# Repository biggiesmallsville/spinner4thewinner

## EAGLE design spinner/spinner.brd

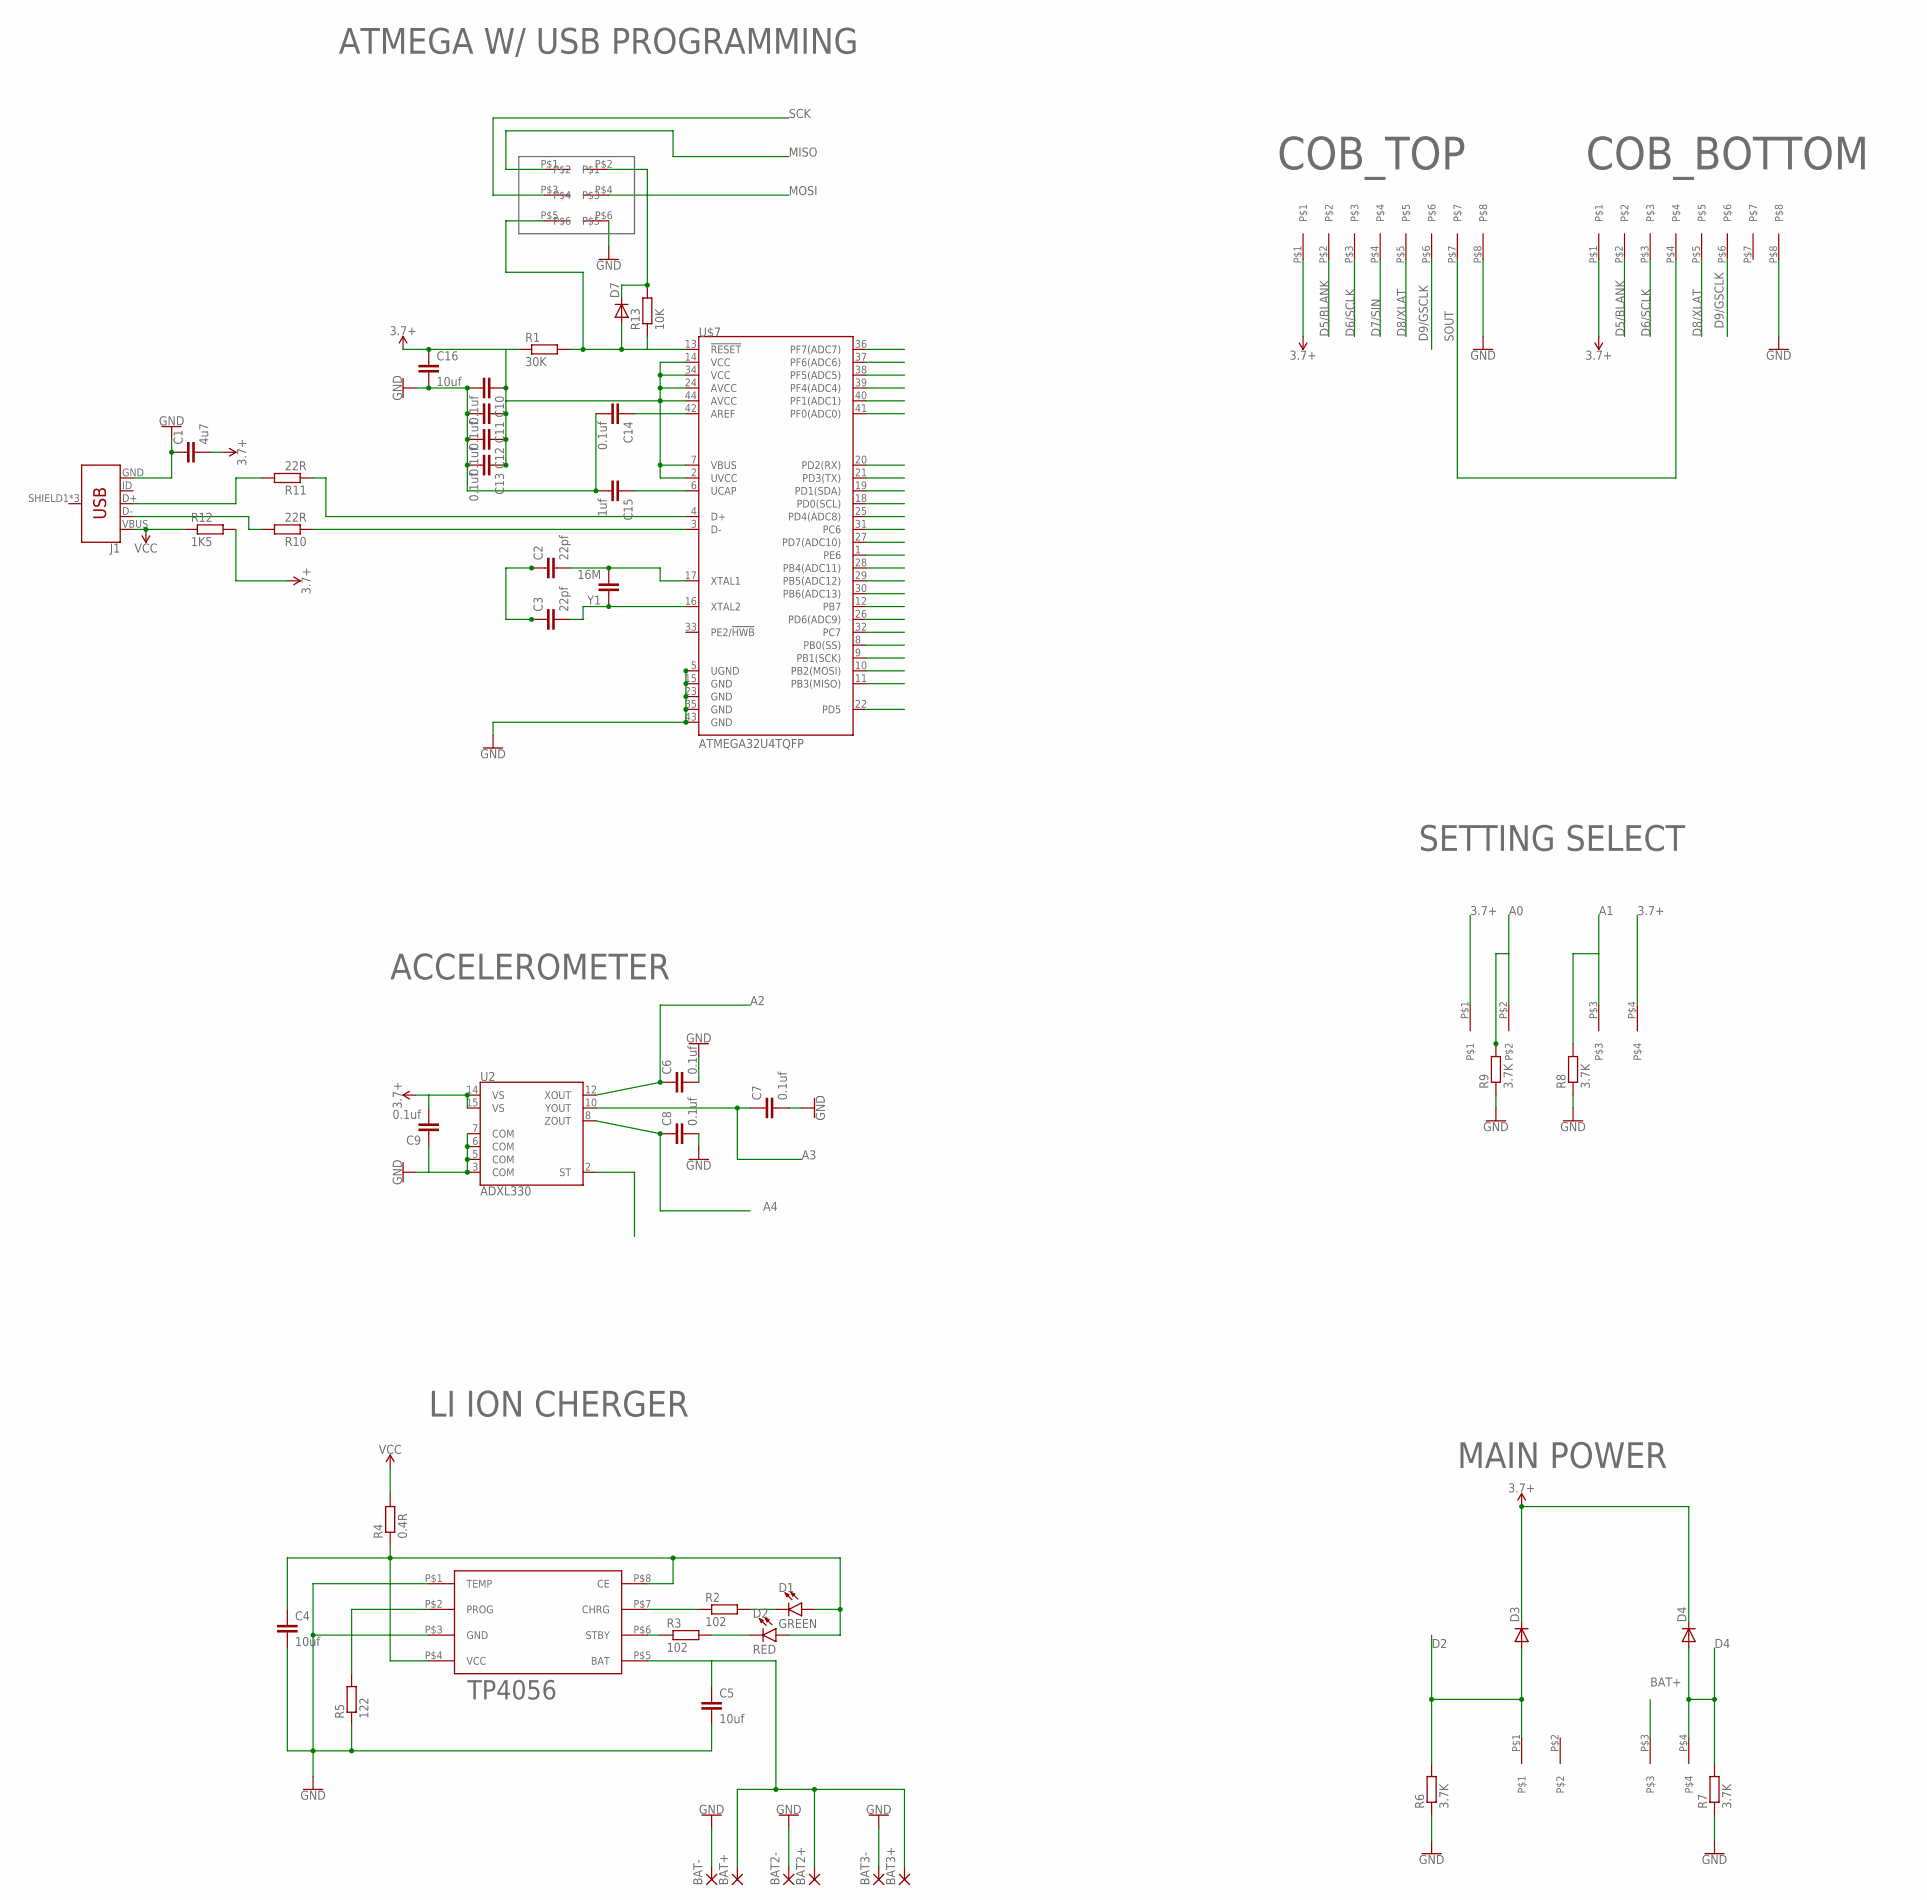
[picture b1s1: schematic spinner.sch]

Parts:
BAT2+, BAT2-, BAT3+, BAT3-: SMD2; SMD1,27-2,54
BAT+: SMD2; SMD1,27-2,54
BAT-: SMD2; SMD1,27-2,54
C1: 4u7; C0603
C2, C3: 22pf; C0603
C4, C5, C16: 10uf; C0603
C6, C7, C8, C9, C10, C11, C12, C13, C14: 0.1uf; C0603
C15: 1uf; C0603
D1: GREEN; LED-0603
D2: RED; LED-0603
D3, D4, D7: DIODE-SOD123; SOD123
J1: USB_MICRO-BREDUCED_PASTE; USB-B-MICRO-SMD_RED_PASTE
R1: 30K; R0603
R2, R3: 102; R0603
R4: 0.4R; R0603
R5: 122; R0603
R6, R7, R8, R9: 3.7K; R0603
R10, R11: 22R; R0603
R12: 1K5; R0603
R13: 10K; R0603
U2: ADXL330; LFCSP-16-4X4
U$1, U$2: SLIDE_SWITCH
U$3: TP4056
U$6: ICSP
U$7: ATMEGA32U4TQFP; SPARKFUN-DIGITALIC_TQFP44
U$8, U$9: 8PIN
Y1: 16M; C0603

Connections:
3.7+: C1.2, C9.2, C10.1, C11.1, C12.1, C13.1, C16.1, D3.C, D4.C, R1.1, R12.2, U2.14 (VS), U2.15 (VS), U$1.P$1, U$1.P$4, U$7.2 (UVCC), U$7.7 (VBUS), U$7.14 (VCC), U$7.24 (AVCC), U$7.34 (VCC), U$7.44 (AVCC), U$8.P$1, U$9.P$1
A0: R9.2, U$1.P$2, U$7.36 (PF7(ADC7))
A1: R8.2, U$1.P$3, U$7.37 (PF6(ADC6))
A2: C6.1, U2.12 (XOUT), U$7.38 (PF5(ADC5))
A3: C7.1, U2.10 (YOUT), U$7.39 (PF4(ADC4))
A4: C8.1, U2.8 (ZOUT), U$7.40 (PF1(ADC1))
A5: U$7.41 (PF0(ADC0))
BAT+: BAT2+.1, BAT3+.1, BAT+.1, C5.1, U$2.P$3, U$3.P$5 (BAT)
D0: U$7.20 (PD2(RX))
D1: U$7.21 (PD3(TX))
D2: D3.A, R6.2, U$2.P$1, U$7.19 (PD1(SDA))
D3: U$7.18 (PD0(SCL))
D4: D4.A, R7.2, U$2.P$4, U$7.25 (PD4(ADC8))
D5/BLANK: U$7.31 (PC6), U$8.P$2, U$9.P$2
D6/SCLK: U$7.27 (PD7(ADC10)), U$8.P$3, U$9.P$3
D7/SIN: U$7.1 (PE6), U$8.P$4
D8/XLAT: U$7.28 (PB4(ADC11)), U$8.P$5, U$9.P$5
D9/GSCLK: R11.1, U$7.4 (D+), U$7.29 (PB5(ADC12)), U$8.P$6, U$9.P$6
D10: U$7.30 (PB6(ADC13))
D11: U$7.12 (PB7)
D12: U$7.26 (PD6(ADC9))
D13: U$7.32 (PC7)
D17: U$7.8 (PB0(SS))
GND: BAT2-.1, BAT3-.1, BAT-.1, C1.1, C2.1, C3.1, C4.2, C5.2, C6.2, C7.2, C8.2, C9.1, C10.2, C11.2, C12.2, C13.2, C14.2, C15.2, C16.2, J1.GND, R5.1, R6.1, R7.1, R8.1, R9.1, U2.3 (COM), U2.5 (COM), U2.6 (COM), U2.7 (COM), U$3.P$1 (TEMP), U$3.P$3 (GND), U$6.P$6, U$7.5 (UGND), U$7.15 (GND), U$7.23 (GND), U$7.35 (GND), U$7.43 (GND), U$8.P$8, U$9.P$8
MISO: U$6.P$1, U$7.11 (PB3(MISO))
MOSI: U$6.P$4, U$7.10 (PB2(MOSI))
unnamed: C2.2, U$7.17 (XTAL1), Y1.2
unnamed: C3.2, U$7.16 (XTAL2), Y1.1
unnamed: D7.C, R13.2, U$6.P$2
unnamed: R5.2, U$3.P$2 (PROG)
unnamed: C4.1, D1.A, D2.A, R4.1, U$3.P$4 (VCC), U$3.P$8 (CE)
unnamed: J1.D-, R10.2
unnamed: R2.1, U$3.P$7 (CHRG)
unnamed: R3.1, U$3.P$6 (STBY)
unnamed: D2.C, R3.2
unnamed: D1.C, R2.2
unnamed: J1.D+, R11.2
unnamed: R10.1, U$7.3 (D-)
unnamed: C14.1, U$7.42 (AREF)
unnamed: C15.1, U$7.6 (UCAP)
RESET: D7.A, R1.2, R13.1, U$6.P$5, U$7.13 (!RESET)
SCK: U$6.P$3, U$7.9 (PB1(SCK))
SOUT: U$8.P$7, U$9.P$4
VCC: J1.VBUS, R4.2, R12.1

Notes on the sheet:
COB_TOP
COB_BOTTOM
SETTING SELECT
MAIN POWER
ACCELEROMETER
LI ION CHERGER
ATMEGA W/ USB PROGRAMMING

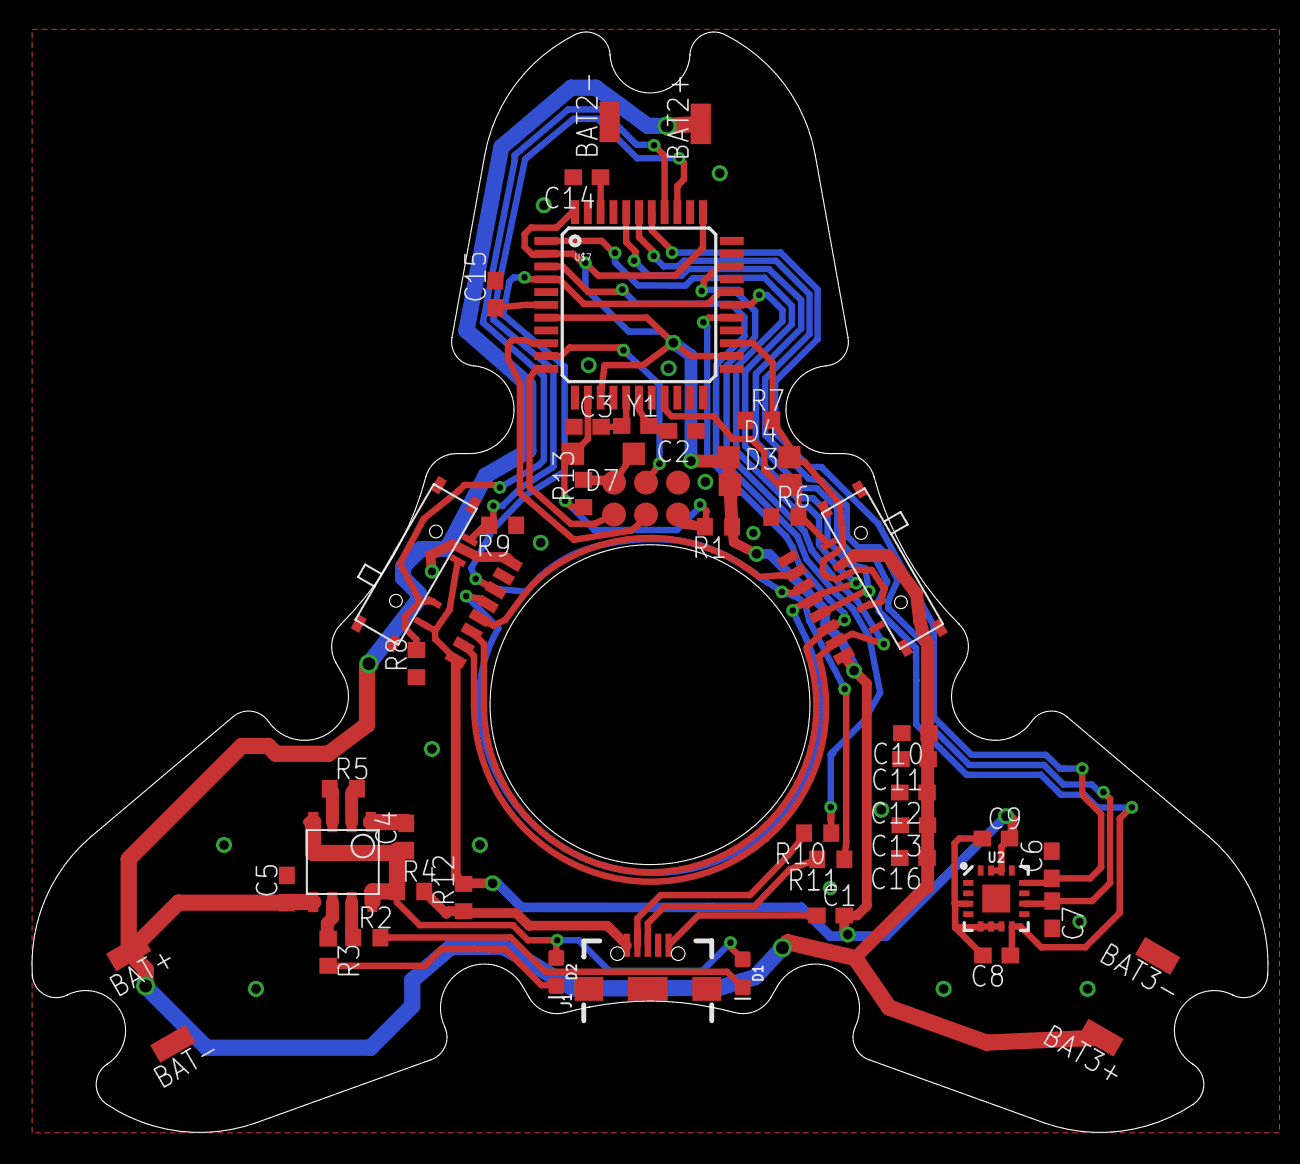
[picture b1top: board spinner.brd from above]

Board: 2 copper layers, 77.3 x 68.8 mm, 50 parts (0 on the bottom side), 35 nets.

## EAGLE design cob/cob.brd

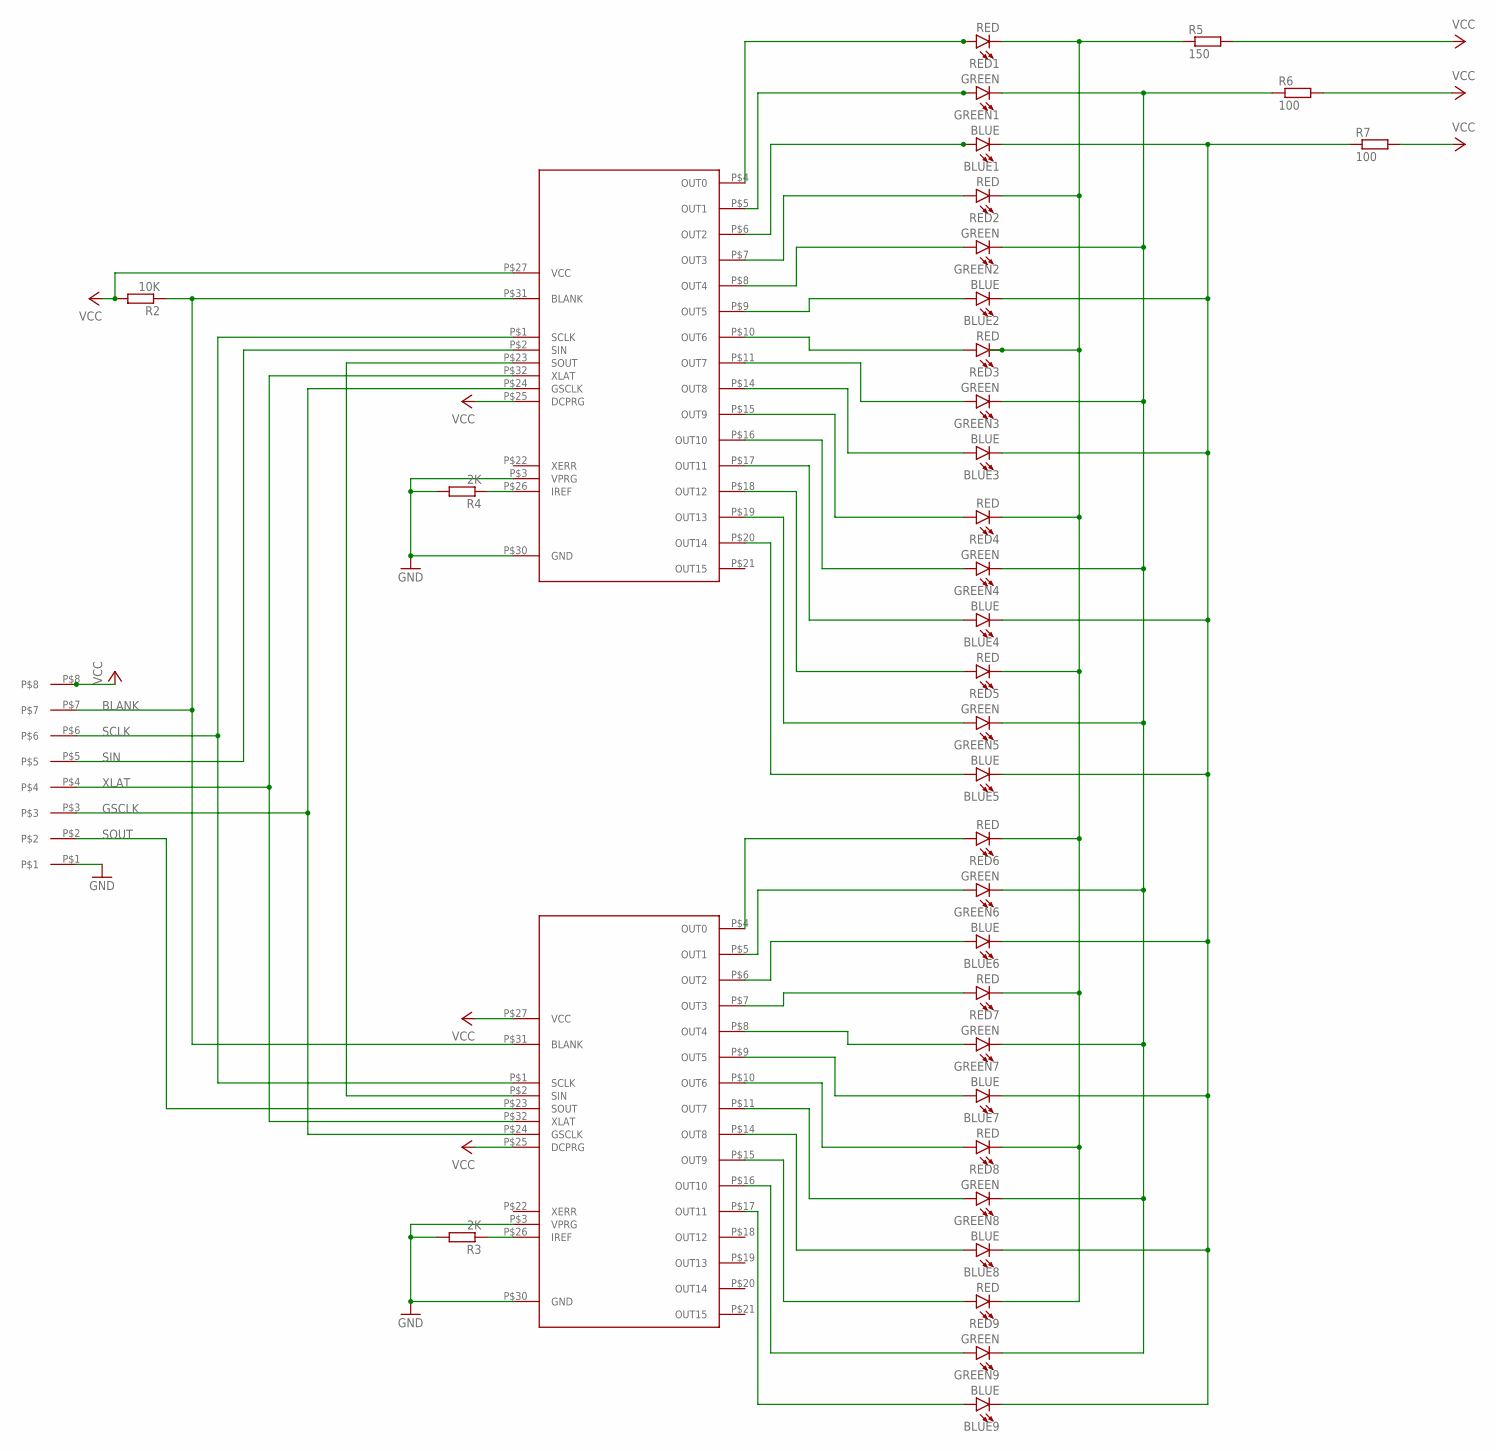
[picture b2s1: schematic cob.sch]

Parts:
BLUE1, BLUE2, BLUE3, BLUE4, BLUE5, BLUE6, BLUE7, BLUE8, BLUE9: BLUE; LED-0603
GREEN1, GREEN2, GREEN3, GREEN4, GREEN5, GREEN6, GREEN7, GREEN8, GREEN9: GREEN; LED-0603
R2: 10K; R0402
R3, R4: 2K; R0402
R5: 150; R1206
R6, R7: 100; R1206
RED1, RED2, RED3, RED4, RED5, RED6, RED7, RED8, RED9: RED; LED-0603
U$1, U$2: TLC5940; RHB
U$3: 8PIN

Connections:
BLANK: R2.1, U$1.P$31 (BLANK), U$2.P$31 (BLANK), U$3.P$7
GND: R3.2, R4.2, U$1.P$3 (VPRG), U$1.P$30 (GND), U$2.P$3 (VPRG), U$2.P$30 (GND), U$3.P$1
GSCLK: U$1.P$24 (GSCLK), U$2.P$24 (GSCLK), U$3.P$3
unnamed: RED1.A, U$1.P$4 (OUT0)
unnamed: GREEN1.A, U$1.P$5 (OUT1)
unnamed: RED2.A, U$1.P$7 (OUT3)
unnamed: R4.1, U$1.P$26 (IREF)
unnamed: R3.1, U$2.P$26 (IREF)
unnamed: BLUE3.A, U$1.P$14 (OUT8)
unnamed: BLUE2.A, U$1.P$9 (OUT5)
unnamed: U$1.P$23 (SOUT), U$2.P$2 (SIN)
unnamed: BLUE1.A, U$1.P$6 (OUT2)
unnamed: GREEN2.A, U$1.P$8 (OUT4)
unnamed: RED3.A, U$1.P$10 (OUT6)
unnamed: GREEN3.A, U$1.P$11 (OUT7)
unnamed: RED4.A, U$1.P$15 (OUT9)
unnamed: GREEN4.A, U$1.P$16 (OUT10)
unnamed: BLUE4.A, U$1.P$17 (OUT11)
unnamed: RED5.A, U$1.P$18 (OUT12)
unnamed: GREEN5.A, U$1.P$19 (OUT13)
unnamed: BLUE5.A, U$1.P$20 (OUT14)
unnamed: BLUE6.A, U$2.P$6 (OUT2)
unnamed: GREEN6.A, U$2.P$5 (OUT1)
unnamed: RED6.A, U$2.P$4 (OUT0)
unnamed: RED7.A, U$2.P$7 (OUT3)
unnamed: GREEN7.A, U$2.P$8 (OUT4)
unnamed: BLUE7.A, U$2.P$9 (OUT5)
unnamed: RED8.A, U$2.P$10 (OUT6)
unnamed: GREEN8.A, U$2.P$11 (OUT7)
unnamed: BLUE8.A, U$2.P$14 (OUT8)
unnamed: BLUE9.A, U$2.P$17 (OUT11)
unnamed: GREEN9.A, U$2.P$16 (OUT10)
unnamed: RED9.A, U$2.P$15 (OUT9)
unnamed: R5.1, RED1.C, RED2.C, RED3.C, RED4.C, RED5.C, RED6.C, RED7.C, RED8.C, RED9.C
unnamed: GREEN1.C, GREEN2.C, GREEN3.C, GREEN4.C, GREEN5.C, GREEN6.C, GREEN7.C, GREEN8.C, GREEN9.C, R6.1
unnamed: BLUE1.C, BLUE2.C, BLUE3.C, BLUE4.C, BLUE5.C, BLUE6.C, BLUE7.C, BLUE8.C, BLUE9.C, R7.1
SCLK: U$1.P$1 (SCLK), U$2.P$1 (SCLK), U$3.P$6
SIN: U$1.P$2 (SIN), U$3.P$5
SOUT: U$2.P$23 (SOUT), U$3.P$2
VCC: R2.2, R5.2, R6.2, R7.2, U$1.P$25 (DCPRG), U$1.P$27 (VCC), U$2.P$25 (DCPRG), U$2.P$27 (VCC), U$3.P$8
XLAT: U$1.P$32 (XLAT), U$2.P$32 (XLAT), U$3.P$4

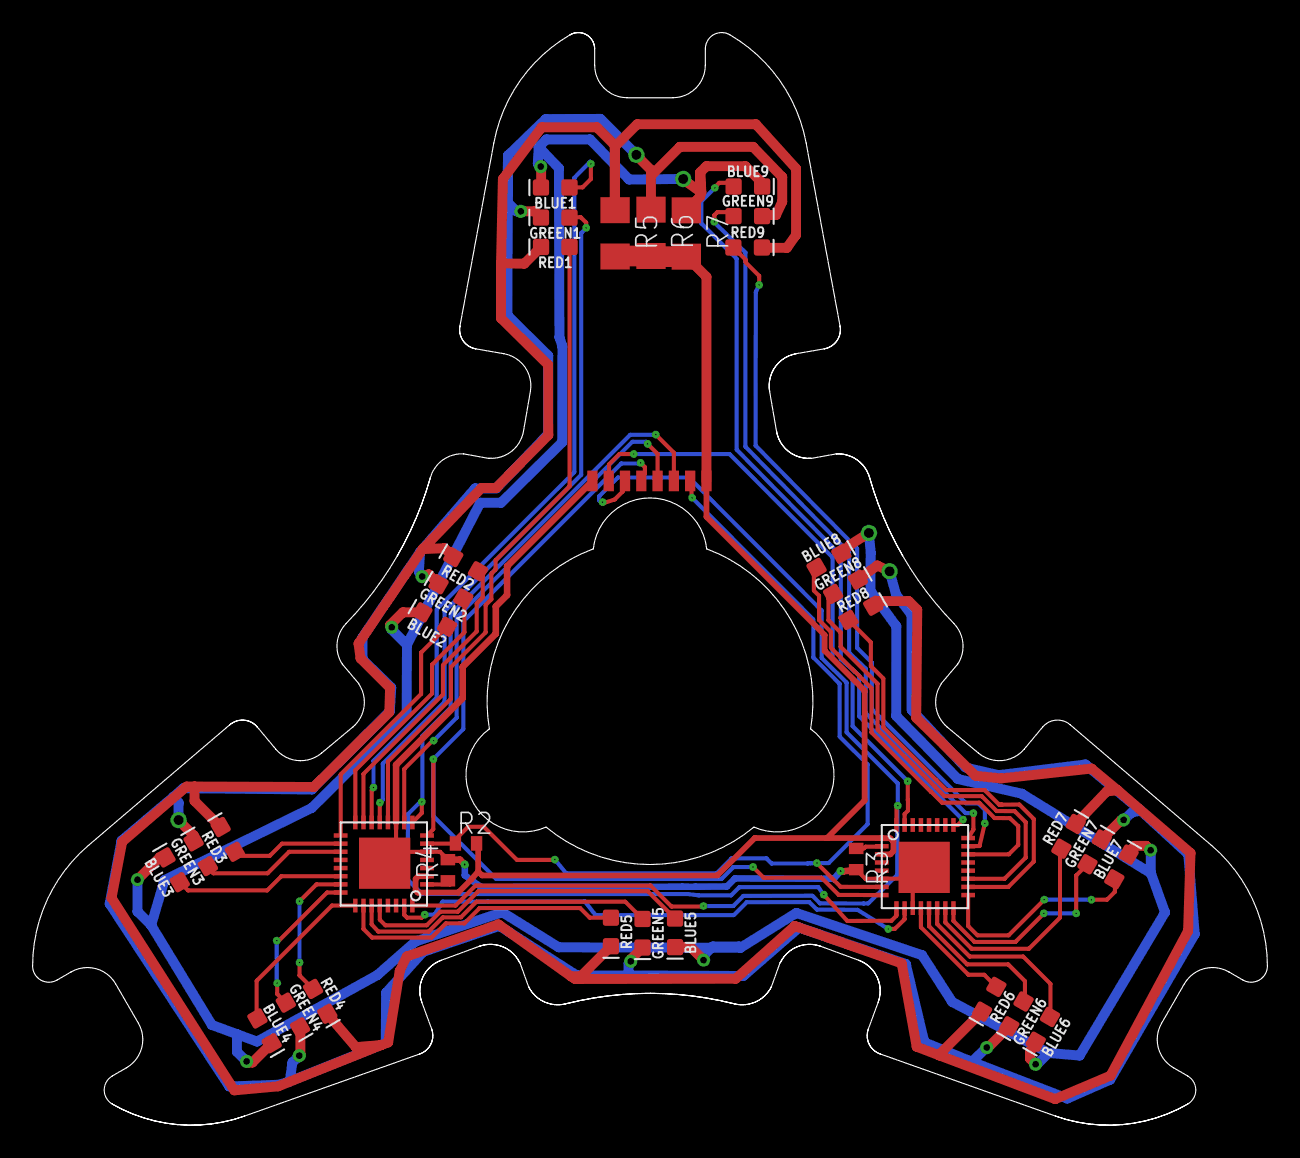
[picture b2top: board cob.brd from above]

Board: 2 copper layers, 75.8 x 67.1 mm, 36 parts (0 on the bottom side), 41 nets.

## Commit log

2017-05-11 test update
2017-05-11 added resources
2017-05-11 fixed connections to cob board
2017-05-16 laid out traces on spinner brd
2017-05-16 added images for report
2017-05-16 added .lck in git ignore, add more images in reports folder, and added DRC folder with 2 layer DRC file.
2017-05-16 added images for reports.

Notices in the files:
parts and their libraries:
SparkFun-LED: Licensing: Creative Commons ShareAlike 4.0 International - https://creativecommons.org/licenses/by-sa/4.0
